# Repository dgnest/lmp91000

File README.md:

# Using the LMP91000 gas sensor with Arduino

The LMP91000 is a programmable Analog Front End (AFE) for use in micro-power electrochemical sensing applications... [+ info about it](http://www.ti.com/product/lmp91000 "more info")

He we use this great gas sensor alongside an Arduino Mega 2560.

[datasheet](http://www.ti.com/lit/ds/symlink/lmp91000.pdf "datasheet")

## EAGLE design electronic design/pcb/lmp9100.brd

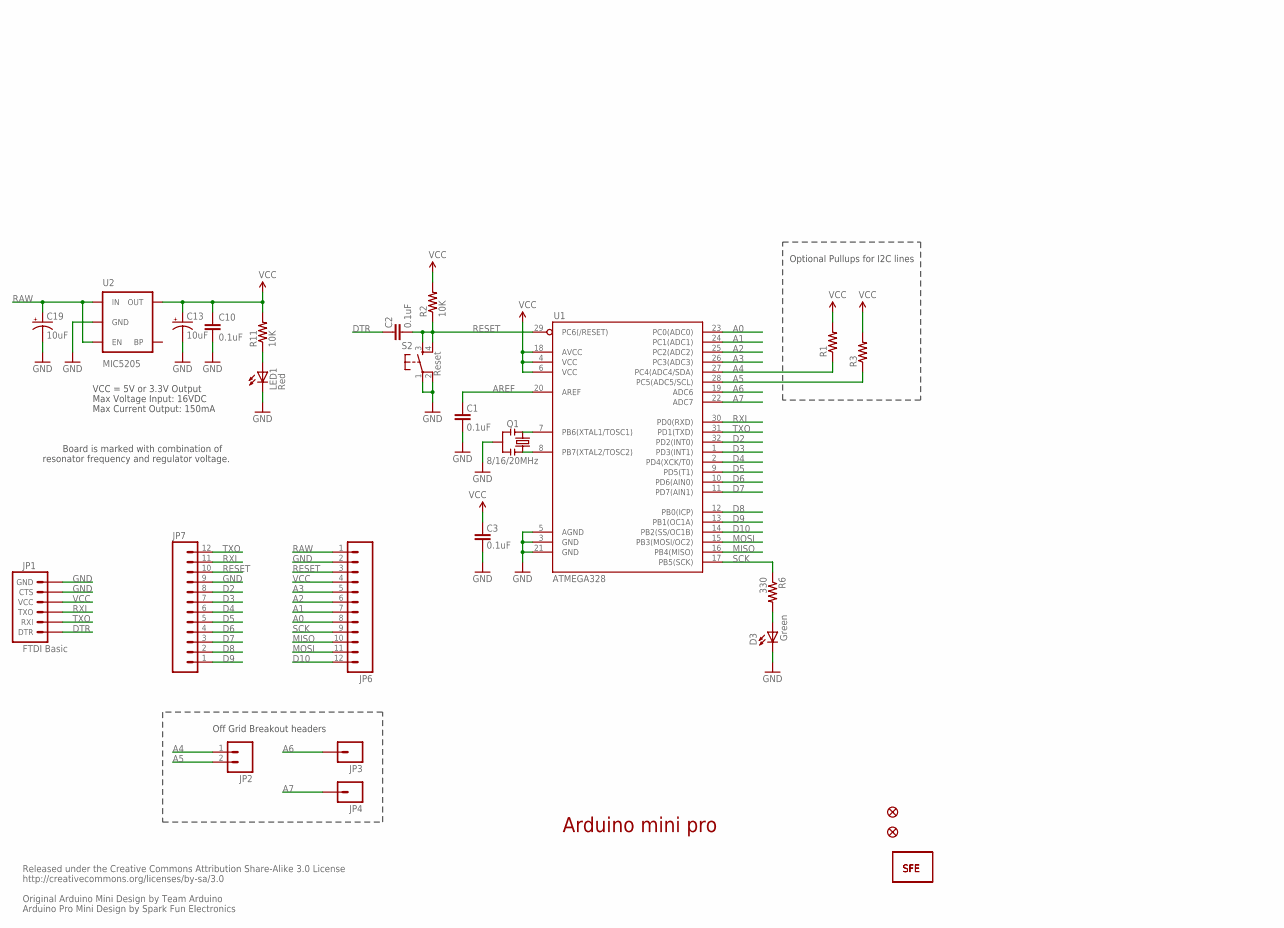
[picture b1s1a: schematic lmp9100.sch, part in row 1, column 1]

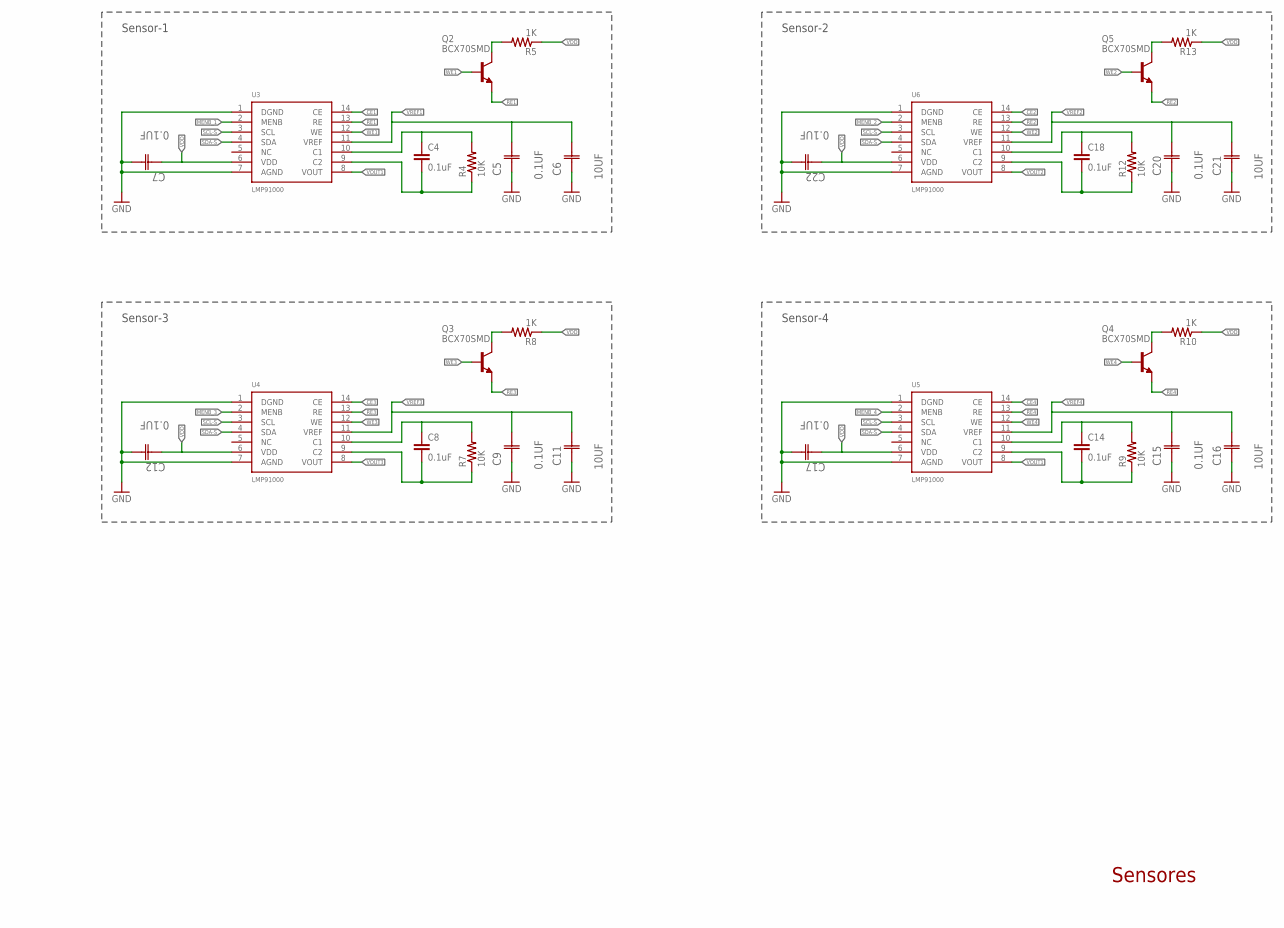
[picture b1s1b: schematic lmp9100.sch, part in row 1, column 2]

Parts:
C1, C2, C3, C4, C8, C10, C14, C18: 0.1uF; 0402-CAP
C5, C7, C9, C12, C15, C17, C20, C22: 0.1UF; CAPC1608X90N
C6, C11, C16, C21: 10UF; CAPC3216X178N
C13, C19: 10uF; EIA3216
D3: Green; LED-0603
JP1: FTDI Basic; 1X06
JP2: M02PTH; 1X02
JP3, JP4: M01PTH; 1X01
JP5, JP8: FIDUCIALUFIDUCIAL; MICRO-FIDUCIAL
JP6, JP7: M12PTH; 1X12
LED1: Red; LED-0603
Q1: 8/16/20MHz; RESONATOR-SMD
Q2, Q3, Q4, Q5: BCX70SMD; SOT23
R1, R3: RESISTOR0402-RES; 0402-RES
R2, R4, R7, R9, R11, R12: 10K; 0402-RES
R5, R8, R10, R13: 1K; 0402-RES
R6: 330; 0402-RES
S2: Reset; TACTILE_SWITCH_SMD
U1: ATMEGA328; TQFP32-08
U2: MIC5205; SOT23-5
U3, U4, U5, U6: LMP91000
U$1: LOGO-SFESK; SFE-LOGO-FLAME
U$11: LOGO-SFENEW; SFE-NEW-WEBLOGO

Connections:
A0: JP6.8, U1.23 (PC0(ADC0))
A1: JP6.7, U1.24 (PC1(ADC1))
A2: JP6.6, U1.25 (PC2(ADC2))
A3: JP6.5, U1.26 (PC3(ADC3))
A4: JP2.1, R1.1, U1.27 (PC4(ADC4/SDA))
A5: JP2.2, R3.1, U1.28 (PC5(ADC5/SCL))
A6: JP3.1, U1.19 (ADC6)
A7: JP4.1, U1.22 (ADC7)
AREF: C1.2, U1.20 (AREF)
CE1: U3.14 (CE)
CE2: U6.14 (CE)
CE3: U4.14 (CE)
CE4: U5.14 (CE)
D2: JP7.8, U1.32 (PD2(INT0))
D3: JP7.7, U1.1 (PD3(INT1))
D4: JP7.6, U1.2 (PD4(XCK/T0))
D5: JP7.5, U1.9 (PD5(T1))
D6: JP7.4, U1.10 (PD6(AIN0))
D7: JP7.3, U1.11 (PD7(AIN1))
D8: JP7.2, U1.12 (PB0(ICP))
D9: JP7.1, U1.13 (PB1(OC1A))
D10: JP6.12, U1.14 (PB2(SS/OC1B))
DTR: C2.2, JP1.1 (DTR)
GND: C1.1, C3.1, C5.1 (C1), C6.1 (C1), C7.2 (C2), C9.1 (C1), C10.2, C11.1 (C1), C12.2 (C2), C13.C (-), C15.1 (C1), C16.1 (C1), C17.2 (C2), C19.C (-), C20.1 (C1), C21.1 (C1), C22.2 (C2), D3.C, JP1.5 (CTS), JP1.6 (GND), JP6.2, JP7.9, LED1.C, Q1.2, S2.1, S2.2, U1.3 (GND), U1.5 (AGND), U1.21 (GND), U2.2 (GND), U3.1 (DGND), U3.7 (AGND), U4.1 (DGND), U4.7 (AGND), U5.1 (DGND), U5.7 (AGND), U6.1 (DGND), U6.7 (AGND)
MENB_1: U3.2 (MENB)
MENB_2: U6.2 (MENB)
MENB_3: U4.2 (MENB)
MENB_4: U5.2 (MENB)
MISO: JP6.10, U1.16 (PB4(MISO))
MOSI: JP6.11, U1.15 (PB3(MOSI/OC2))
unnamed: Q1.1, U1.8 (PB7(XTAL2/TOSC2))
unnamed: Q1.3, U1.7 (PB6(XTAL1/TOSC1))
unnamed: C4.2, R4.1, U3.9 (C2)
unnamed: C4.1, R4.2, U3.10 (C1)
unnamed: Q2.3 (C), R5.2
unnamed: C8.2, R7.1, U4.9 (C2)
unnamed: D3.A, R6.2
unnamed: C8.1, R7.2, U4.10 (C1)
unnamed: Q3.3 (C), R8.2
unnamed: C14.2, R9.1, U5.9 (C2)
unnamed: C14.1, R9.2, U5.10 (C1)
unnamed: Q4.3 (C), R10.2
unnamed: C18.2, R12.1, U6.9 (C2)
unnamed: C18.1, R12.2, U6.10 (C1)
unnamed: Q5.3 (C), R13.2
unnamed: LED1.A, R11.1
RAW: C19.A (+), JP6.1, U2.1 (IN), U2.3 (EN)
RE1: Q2.2 (E), U3.13 (RE)
RE2: Q5.2 (E), U6.13 (RE)
RE3: Q3.2 (E), U4.13 (RE)
RE4: Q4.2 (E), U5.13 (RE)
RESET: C2.1, JP6.3, JP7.10, R2.1, S2.3, S2.4, U1.29 (PC6(/RESET))
RXI: JP1.3 (TXO), JP7.11, U1.30 (PD0(RXD))
SCK: JP6.9, R6.1, U1.17 (PB5(SCK))
SCL-S: U3.3 (SCL), U4.3 (SCL), U5.3 (SCL), U6.3 (SCL)
SDA-S: U3.4 (SDA), U4.4 (SDA), U5.4 (SDA), U6.4 (SDA)
TXO: JP1.2 (RXI), JP7.12, U1.31 (PD1(TXD))
VCC: C3.2, C10.1, C13.A (+), JP1.4 (VCC), JP6.4, R1.2, R2.2, R3.2, R11.2, U1.4 (VCC), U1.6 (VCC), U1.18 (AVCC), U2.5 (OUT)
VDD: C7.1 (C1), C12.1 (C1), C17.1 (C1), C22.1 (C1), R5.1, R8.1, R10.1, R13.1, U3.6 (VDD), U4.6 (VDD), U5.6 (VDD), U6.6 (VDD)
VOUT1: U3.8 (VOUT), U5.8 (VOUT)
VOUT2: U6.8 (VOUT)
VOUT3: U4.8 (VOUT)
VREF1: C5.2 (C2), C6.2 (C2), U3.11 (VREF)
VREF2: C20.2 (C2), C21.2 (C2), U6.11 (VREF)
VREF3: C9.2 (C2), C11.2 (C2), U4.11 (VREF)
VREF4: C15.2 (C2), C16.2 (C2), U5.11 (VREF)
WE1: Q2.1 (B), U3.12 (WE)
WE2: Q5.1 (B), U6.12 (WE)
WE3: Q3.1 (B), U4.12 (WE)
WE4: Q4.1 (B), U5.12 (WE)

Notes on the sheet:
Released under the Creative Commons Attribution Share-Alike 3.0 License
http://creativecommons.org/licenses/by-sa/3.0
Original Arduino Mini Design by Team Arduino
Arduino Pro Mini Design by Spark Fun Electronics
Max Voltage Input: 16VDC
Max Current Output: 150mA
Board is marked with combination of
resonator frequency and regulator voltage.
VCC = 5V or 3.3V Output
Optional Pullups for I2C lines
Off Grid Breakout headers
Sensor-1
Sensor-3
Sensor-4
Sensor-2
Sensores
Arduino mini pro

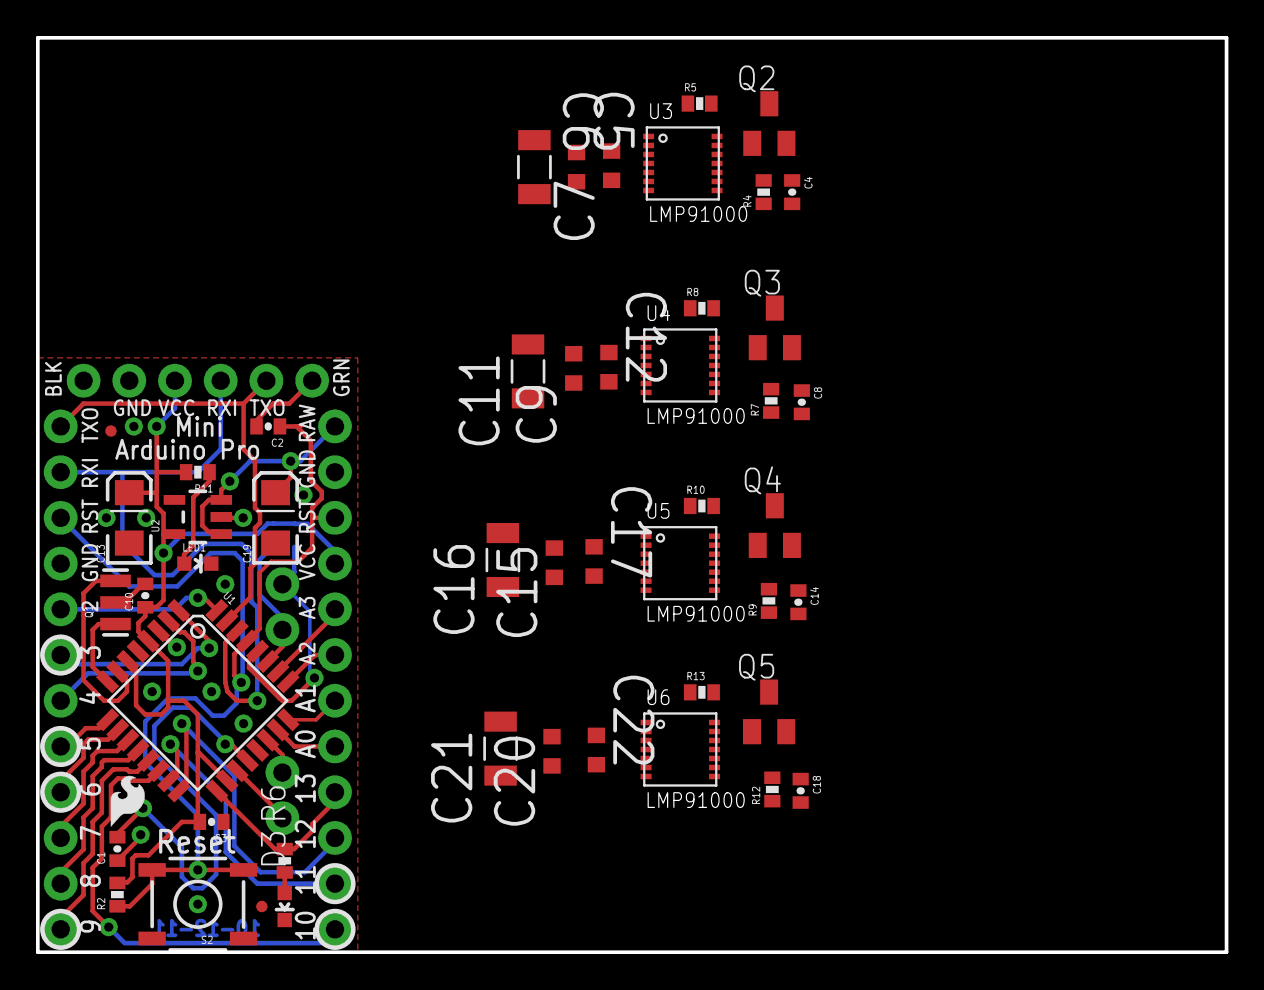
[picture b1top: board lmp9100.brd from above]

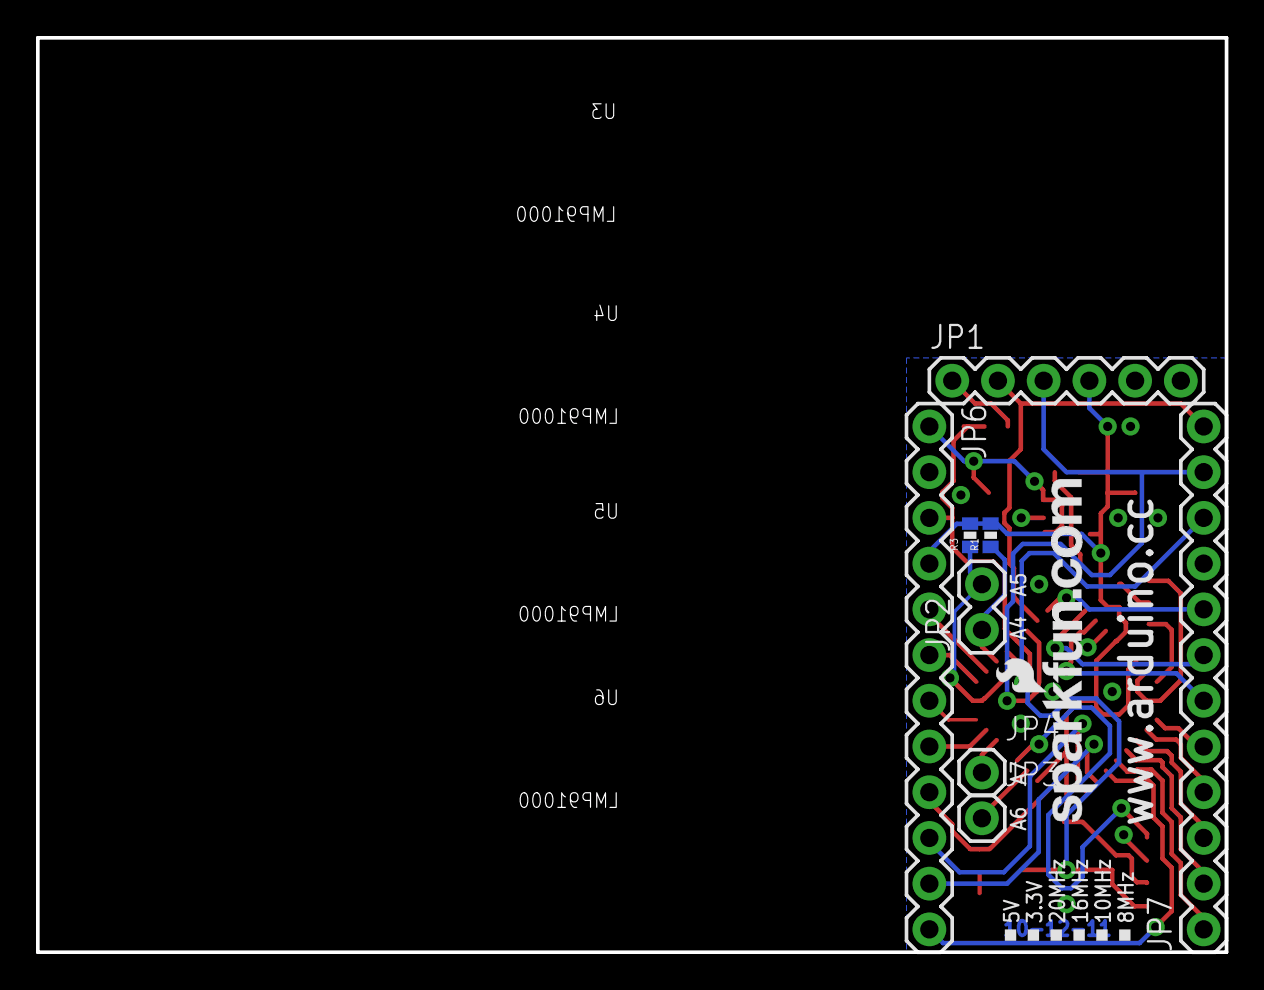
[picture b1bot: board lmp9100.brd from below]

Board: 2 copper layers, 66.0 x 50.8 mm, 59 parts (9 on the bottom side), 60 nets.

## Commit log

2014-12-16 add arduino source file, readme and an empty gitignore :)
2015-01-08 add gitignore
2015-01-08 add python requirements
2015-01-08 change arduino's source files scaffolding
2015-01-08 add python serial client
2015-01-09 refactoring code
2015-01-09 add stop byte. Refactoring code
2015-01-09 change input message
2015-01-11 refactoring Frame library
2015-01-11 fix header
2015-01-11 send frame with valid options
2015-01-11 refactor frame libray. Add new library to handle the sensor: lm91000
2015-01-14 refactoring lmp91000 library
2015-01-15 add readRegister method and hardcode to send a fixed register
2015-01-16 change String and chars by vector and byte types
2015-01-27 add electronic design
